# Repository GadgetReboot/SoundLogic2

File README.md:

# SoundLogic2
<br><br><BR><BR>
555 sound effects with NAND gates and a binary counter

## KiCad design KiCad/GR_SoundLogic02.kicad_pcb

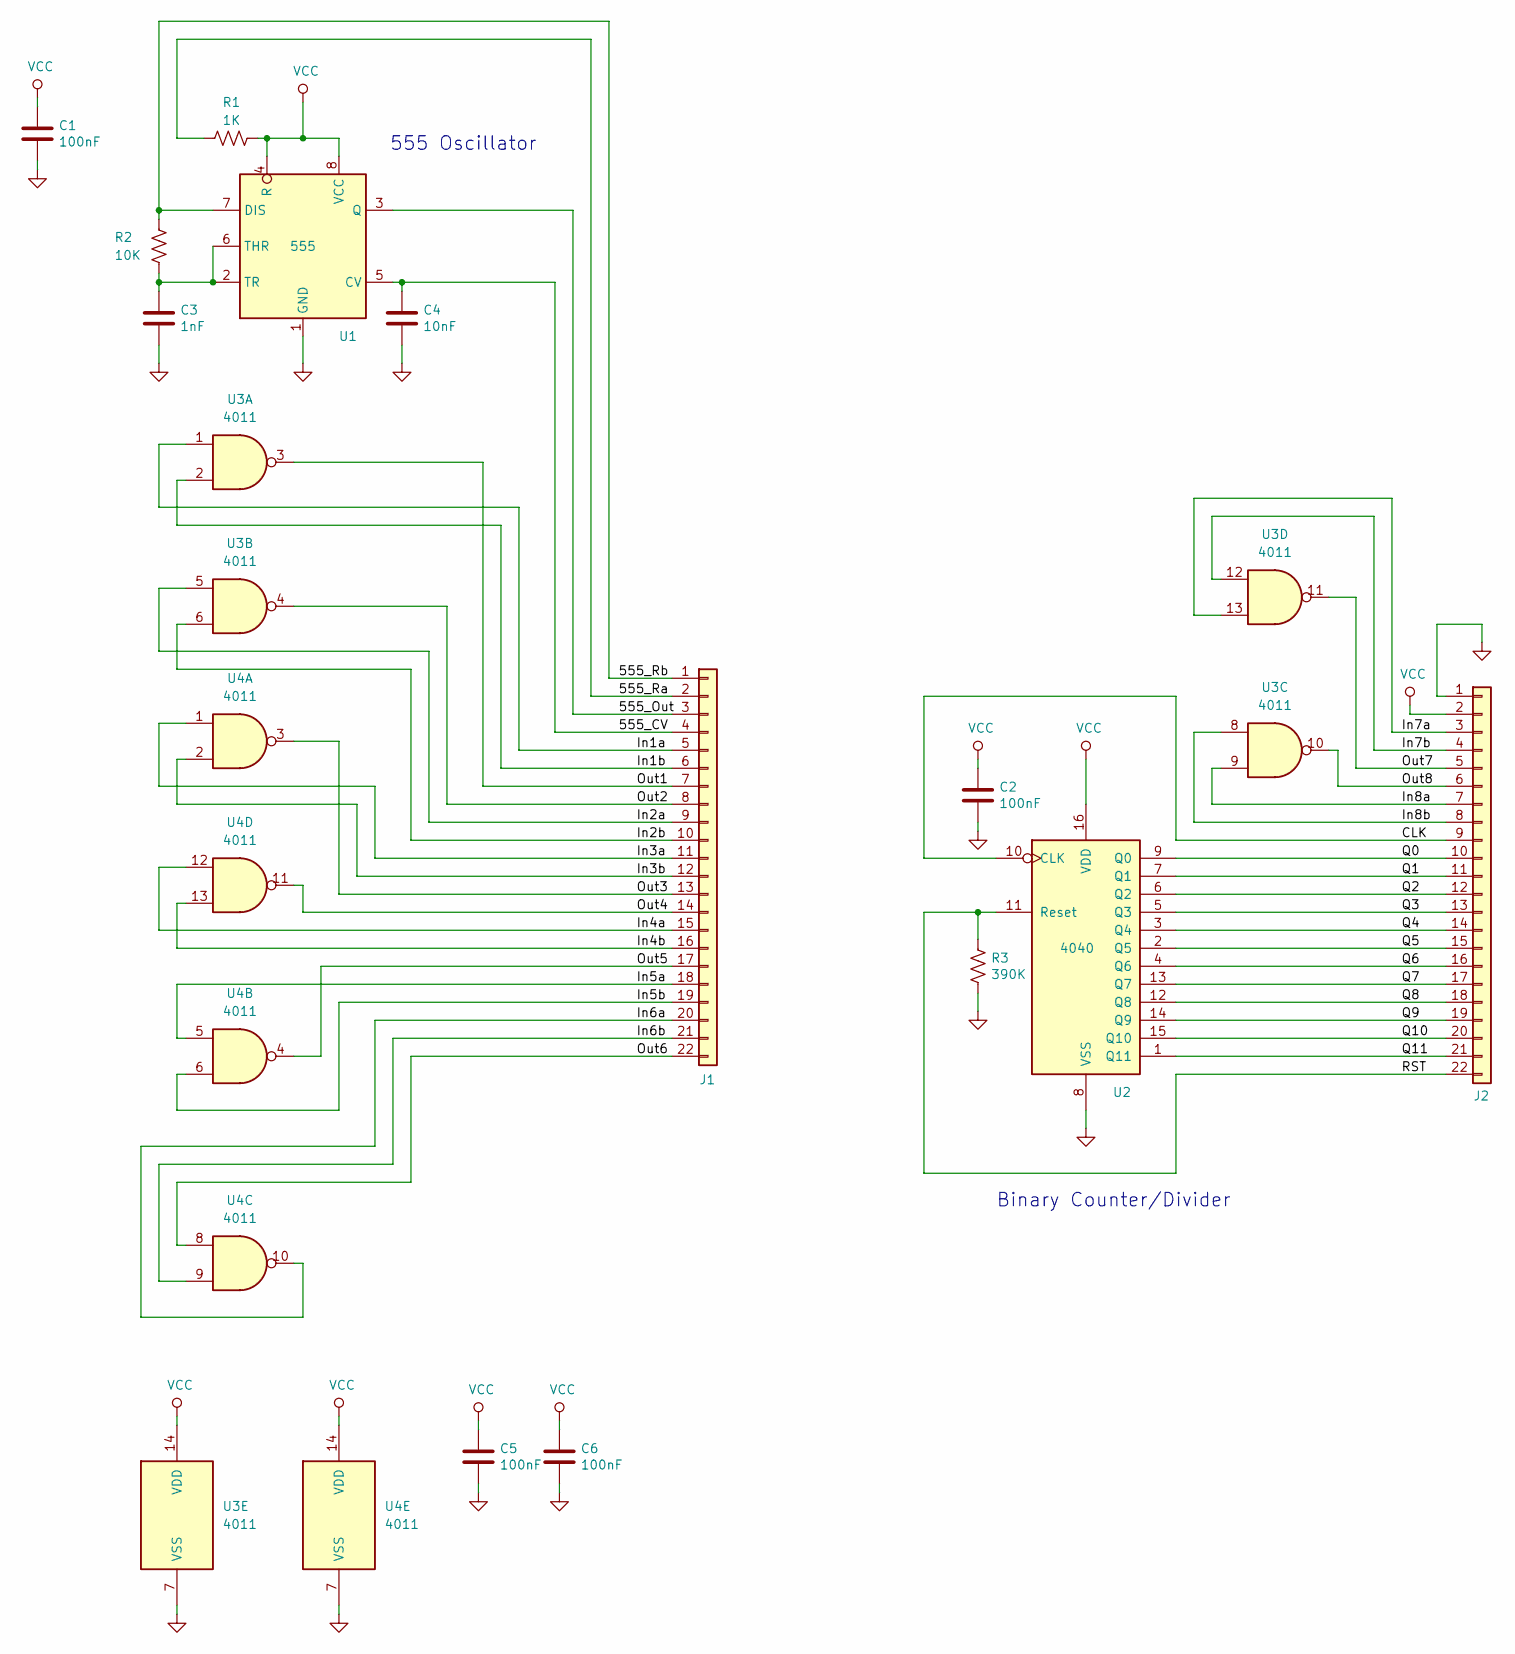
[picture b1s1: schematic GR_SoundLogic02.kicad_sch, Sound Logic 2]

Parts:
C1, C2, C5, C6: 100nF; C_0805_2012Metric_Pad1.18x1.45mm_HandSolder
C3: 1nF; C_0805_2012Metric_Pad1.18x1.45mm_HandSolder
C4: 10nF; C_0805_2012Metric_Pad1.18x1.45mm_HandSolder
J1, J2: Conn_01x22; PinHeader_1x22_P2.54mm_Vertical
R1: 1K; R_0805_2012Metric_Pad1.20x1.40mm_HandSolder
R2: 10K; R_0805_2012Metric_Pad1.20x1.40mm_HandSolder
R3: 390K; R_0805_2012Metric_Pad1.20x1.40mm_HandSolder
U1: 555; SOIC-8_3.9x4.9mm_P1.27mm
U2: 4040; SOIC-16_3.9x9.9mm_P1.27mm
U3, U4: 4011; SO-14_3.9x8.65mm_P1.27mm

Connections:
/555_CV: C4.1, J1.4, U1.5 (CV)
/555_Out: J1.3, U1.3 (Q)
/555_Ra: J1.2, R1.2
/555_Rb: J1.1, R2.1, U1.7 (DIS)
/CLK: J2.9, U2.10 (CLK)
/In1a: J1.5, U3.1
/In1b: J1.6, U3.2
/In2a: J1.9, U3.5
/In2b: J1.10, U3.6
/In3a: J1.11, U4.1
/In3b: J1.12, U4.2
/In4a: J1.15, U4.12
/In4b: J1.16, U4.13
/In5a: J1.18, U4.5
/In5b: J1.19, U4.6
/In6a: J1.20, U4.10
/In6b: J1.21, U4.9
/In7a: J2.3, U3.13
/In7b: J2.4, U3.12
/In8a: J2.7, U3.9
/In8b: J2.8, U3.8
/Out1: J1.7, U3.3
/Out2: J1.8, U3.4
/Out3: J1.13, U4.3
/Out4: J1.14, U4.11
/Out5: J1.17, U4.4
/Out6: J1.22, U4.8
/Out7: J2.5, U3.11
/Out8: J2.6, U3.10
/Q0: J2.10, U2.9 (Q0)
/Q1: J2.11, U2.7 (Q1)
/Q2: J2.12, U2.6 (Q2)
/Q3: J2.13, U2.5 (Q3)
/Q4: J2.14, U2.3 (Q4)
/Q5: J2.15, U2.2 (Q5)
/Q6: J2.16, U2.4 (Q6)
/Q7: J2.17, U2.13 (Q7)
/Q8: J2.18, U2.12 (Q8)
/Q9: J2.19, U2.14 (Q9)
/Q10: J2.20, U2.15 (Q10)
/Q11: J2.21, U2.1 (Q11)
/RST: J2.22, R3.1, U2.11 (Reset)
GND: C1.2, C2.2, C3.2, C4.2, C5.2, C6.2, J2.1, R3.2, U1.1 (GND), U2.8 (VSS), U3.7 (VSS), U4.7 (VSS)
unnamed: C3.1, R2.2, U1.2 (TR), U1.6 (THR)
VCC: C1.1, C2.1, C5.1, C6.1, J2.2, R1.1, U1.4 (R), U1.8 (VCC), U2.16 (VDD), U3.14 (VDD), U4.14 (VDD)

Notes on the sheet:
555 Oscillator
Binary Counter/Divider

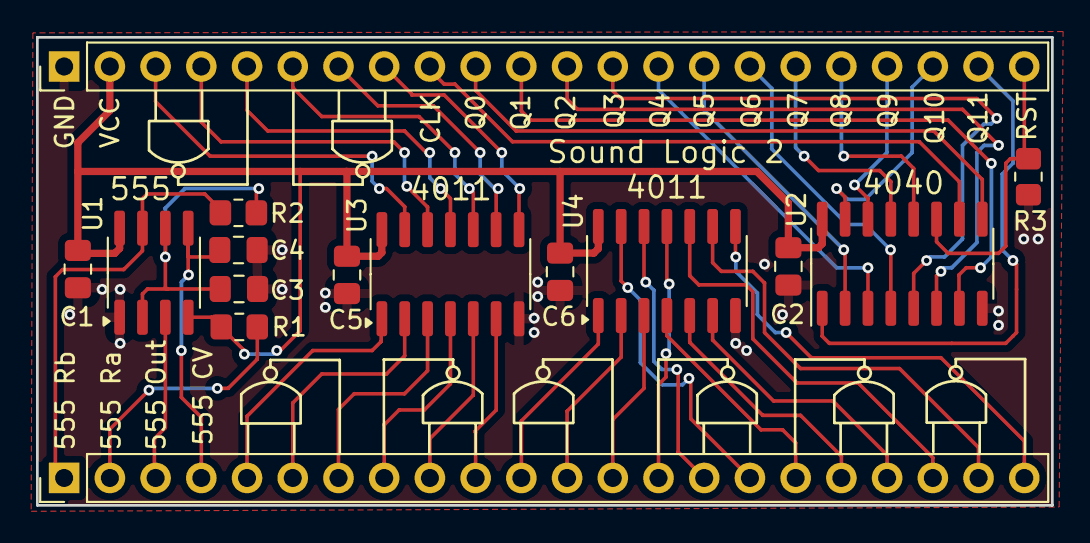
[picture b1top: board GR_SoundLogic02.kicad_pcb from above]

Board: 2 copper layers, 56.4 x 26.0 mm, 15 parts (0 on the bottom side), 45 nets.
